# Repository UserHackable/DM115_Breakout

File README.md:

## breakout 

### Board dimensions

* (162500, 105000) original units
* (1.6250, 1.0500) inches
* (41.2750, 26.6700) mm

| Front | Back |
| --- | --- |
|  |  |

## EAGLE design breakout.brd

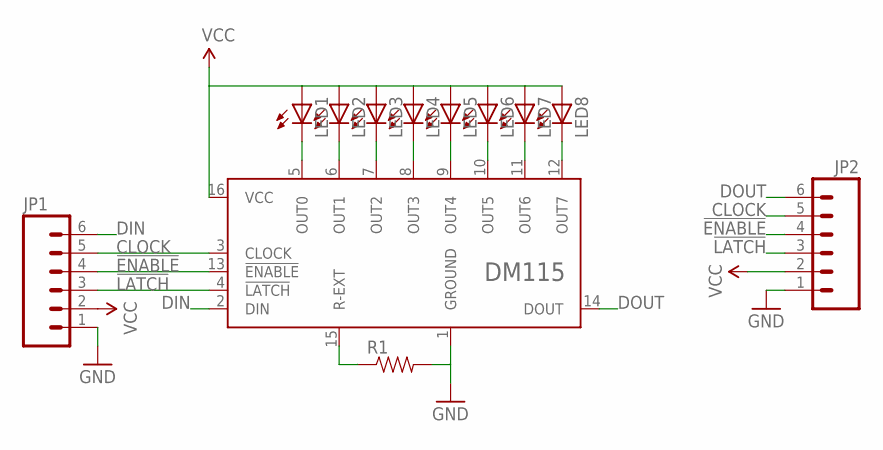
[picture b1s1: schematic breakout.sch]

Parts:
JP1, JP2: M06SIP; 1X06
LED1, LED2, LED3, LED4, LED5, LED6, LED7, LED8: LEDOVAL; LED-OVAL
R1: RESISTORAXIAL-0.3; AXIAL-0.3
U$1: DM115DIP16; DIL16

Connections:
!ENABLE: JP1.4, JP2.4, U$1.13 (!ENABLE)
!LATCH: JP1.3, JP2.3, U$1.4 (!LATCH)
CLOCK: JP1.5, JP2.5, U$1.3 (CLOCK)
DIN: JP1.6, U$1.2 (DIN)
DOUT: JP2.6, U$1.14 (DOUT)
GND: JP1.1, JP2.1, R1.P$2 (2), U$1.1 (GROUND)
unnamed: R1.P$1 (1), U$1.15 (R-EXT)
unnamed: LED1.CATHODE (C), U$1.5 (OUT0)
unnamed: LED2.CATHODE (C), U$1.6 (OUT1)
unnamed: LED3.CATHODE (C), U$1.7 (OUT2)
unnamed: LED4.CATHODE (C), U$1.8 (OUT3)
unnamed: LED5.CATHODE (C), U$1.9 (OUT4)
unnamed: LED6.CATHODE (C), U$1.10 (OUT5)
unnamed: LED7.CATHODE (C), U$1.11 (OUT6)
unnamed: LED8.CATHODE (C), U$1.12 (OUT7)
VCC: JP1.2, JP2.2, LED1.ANODE (A), LED2.ANODE (A), LED3.ANODE (A), LED4.ANODE (A), LED5.ANODE (A), LED6.ANODE (A), LED7.ANODE (A), LED8.ANODE (A), U$1.16 (VCC)

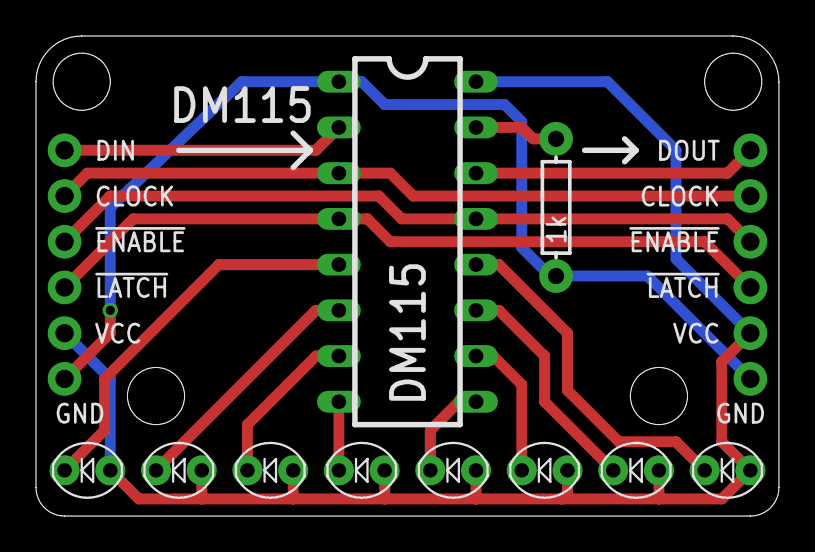
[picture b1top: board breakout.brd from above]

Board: 2 copper layers, 41.3 x 26.7 mm, 12 parts (0 on the bottom side), 16 nets.

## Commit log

2016-04-08 from Makefile
